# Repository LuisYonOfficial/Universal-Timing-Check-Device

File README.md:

# Universal Timing Check Board (UTCB)
###### This repo acts as the digital storage of all associated developments (e.g. firmware, pcb development, CAD) and related documentation (e.g. schematic captures, pictures, testing data) to the "Universal Timing Check Board". This device acts as a sister companion to circuit testing for analog voltage checks and timing. Inspiration for board function and design is from previous revisions of an analog based brake system plausiblity device, however, this device is more general purpose and for my personal use. 

Current Layout: 

## Board Functionality
- Check if an upper threshold is met. (0v to 12v)
    - Multichannel Comparator check
- Check if a lower threshold is met.
    - Multichannel Comparator check (0v to 12v)
- Check if mid threshold comparison between 6 signals is met. 
    - Mid-threshold voltage set via 6 potentiometers (0v to 12v)
- Drive a failure mode signal out from either signals (Within the range of 3.3-12v)
- Give Flashing Red Light when output failure is detected. Otherwise Solid Red.
- Optional: Has breakout OLED slot for visualizing data in real time with bluetooth connected transmitter. Most likely will use STM32 for MCU. 
    
## Board Connection Points

Main PWR: 
- 12V Power In Connector (Gets reduced to 3.3v via regulator for central comparator logic)
- Final PWR voltage needs to be regulated (Using off the shelf dc/dc converters with built-in regulation)

Signal Connections (For reading)
- Terminal block connection points (6P header) for direct wire feeds. 
- OptionaL: For signal voltage reading: Has ribbon cable attachment to breadboard for data collection (but no direct programmable element on-board). 
- For board debugging: Set test points to grip onto for PWR points, Comparator Outputs, and final failure outputs. 
- Indivdual signals, logic set positions, threshold voltages are passed through to the data collection slot for telemetry. 

## Purpose

- Allows me to isolate analog logic voltages on an offboard device or PCB. 
- Allows me to clearly indicate where faulty logic is based on physical tuning via potentiometers. 
- Gives me an automated way of doing logic checks over set number of iterations on the device under test. 

## What to do next
- Add visual LED indicator for each comparator logic output
- Add optional telemetric side port
- Need to reposition test points so as to not accidently short to pot pins.

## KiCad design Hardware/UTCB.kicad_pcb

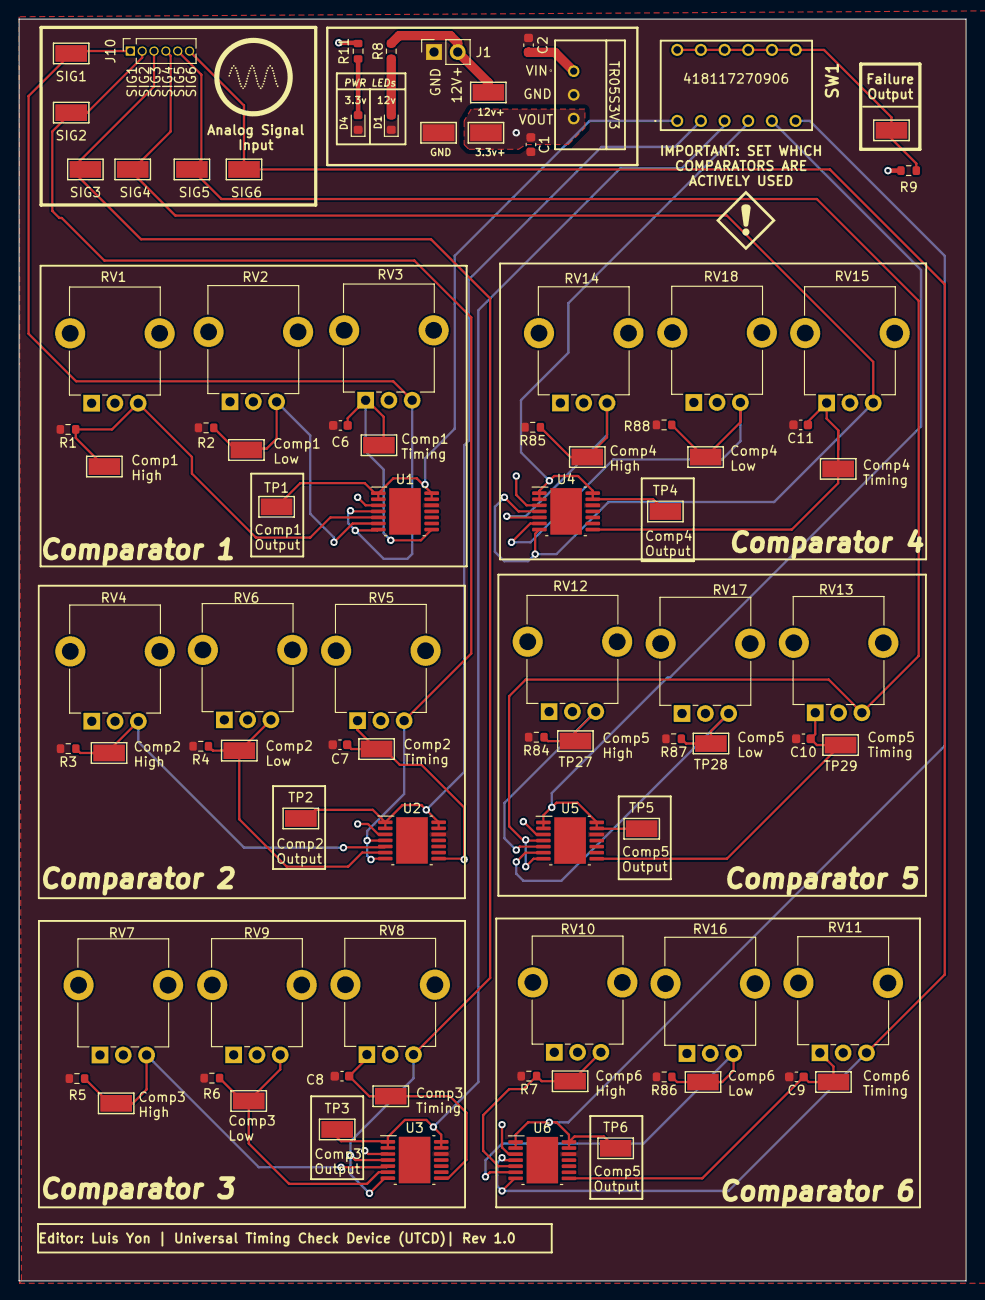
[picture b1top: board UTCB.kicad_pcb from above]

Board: 4 copper layers, 101.6 x 135.4 mm, 87 parts (0 on the bottom side), 36 nets.

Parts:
C1: 47uF; C_0603_1608Metric
C2: 22uF; C_0603_1608Metric
C6, C7, C8, C9, C10, C11: 10uF; C_0603_1608Metric
D1: APT1608SEC/J3-AMT; D_0603_1608Metric
D4: SMLEN3WBC8W1; D_0603_1608Metric
IC1: TR05S3V3
J1: Conn_01x02; PinSocket_1x02_P2.54mm_Vertical
J10: Conn_01x06; PinSocket_1x06_P1.27mm_Vertical
R1, R2, R3, R4, R5, R6, R7, R84, R85, R86, R87, R88: 10kΩ; R_0603_1608Metric
R8, R11: R_Small; R_0603_1608Metric
R9: 1k; R_0603_1608Metric
RV1, RV2, RV4, RV6, RV7, RV9, RV10, RV12, RV14, RV16, RV17, RV18: R_Potentiometer_Trim; Potentiometer_Alpha_RD901F-40-00D_Single_Vertical_CircularH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
RV3, RV5, RV8, RV11, RV13, RV15: 10kΩ; Potentiometer_Alpha_RD901F-40-00D_Single_Vertical_CircularH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
SW1: SW_DIP_x06; 418117270906
TP1: Comp1_Output; TestPoint_Keystone_5015_Micro-Minature
TP2: Comp2_Output; TestPoint_Keystone_5015_Micro-Minature
TP3: Comp3_Output; TestPoint_Keystone_5015_Micro-Minature
TP4: Comp4_Output; TestPoint_Keystone_5015_Micro-Minature
TP5: Comp5_Output; TestPoint_Keystone_5015_Micro-Minature
TP6: Comp6_Output; TestPoint_Keystone_5015_Micro-Minature
TP7: COMP1_HIGH; TestPoint_Keystone_5015_Micro-Minature
TP8: COMP1_LOW; TestPoint_Keystone_5015_Micro-Minature
TP9: COMP1_TIMING; TestPoint_Keystone_5015_Micro-Minature
TP10: COMP2_HIGH; TestPoint_Keystone_5015_Micro-Minature
TP11: COMP2_LOW; TestPoint_Keystone_5015_Micro-Minature
TP12: COMP2_TIMING; TestPoint_Keystone_5015_Micro-Minature
TP13: 12v_Check; TestPoint_Keystone_5015_Micro-Minature
TP14, TP15: COMP3_HIGH; TestPoint_Keystone_5015_Micro-Minature
TP16: 3.3v_Check; TestPoint_Keystone_5015_Micro-Minature
TP17: Signal1_Check; TestPoint_Keystone_5015_Micro-Minature
TP18: Signal2_Check; TestPoint_Keystone_5015_Micro-Minature
TP19: Signal3_Check; TestPoint_Keystone_5015_Micro-Minature
TP20: Signal4_Check; TestPoint_Keystone_5015_Micro-Minature
TP21: Signal5_Check; TestPoint_Keystone_5015_Micro-Minature
TP22: Signal6_Check; TestPoint_Keystone_5015_Micro-Minature
TP23, TP29: COMP3_TIMING; TestPoint_Keystone_5015_Micro-Minature
TP24, TP25: COMP4_HIGH; TestPoint_Keystone_5015_Micro-Minature
TP26: COMP4_TIMING; TestPoint_Keystone_5015_Micro-Minature
TP27, TP28: COMP5_HIGH; TestPoint_Keystone_5015_Micro-Minature
TP30, TP31: COMP6_HIGH; TestPoint_Keystone_5015_Micro-Minature
TP32: COMP6_TIMING; TestPoint_Keystone_5015_Micro-Minature
TP33: Failure_Check; TestPoint_Keystone_5015_Micro-Minature
TP34: GND_Check; TestPoint_Keystone_5015_Micro-Minature
U1, U2, U3, U4, U5, U6: HTSSOP-14-1EP_4.4x5mm_P0.65mm_EP3.4x5mm_Mask3x3.1mm

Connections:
+3.3V: C1.1, IC1.3 (+VOUT), R9.1, R11.1, RV1.1, RV2.1, RV4.1, RV6.1, RV7.1, RV9.1, RV10.1, RV12.1, RV14.1, RV16.1, RV17.1, RV18.1, TP16.1, U1.3 (VCC), U2.3 (VCC), U3.3 (VCC), U4.3 (VCC), U5.3 (VCC), U6.3 (VCC)
+12V: C2.1, IC1.1 (+VIN), J1.2, R8.2, TP13.1
/ComparatorLogic/COMP1_HIGH: R1.1, RV1.3, TP7.1, U1.5 (1IN+)
/ComparatorLogic/COMP1_LOW: R2.1, RV2.3, TP8.1, U1.6 (2IN-)
/ComparatorLogic/COMP2_HIGH: R3.1, RV4.3, TP10.1, U2.5 (1IN+)
/ComparatorLogic/COMP2_LOW: R4.1, RV6.3, TP11.1, U2.6 (2IN-)
/ComparatorLogic/COMP3_HIGH: R5.1, RV7.3, TP14.1, U3.5 (1IN+)
/ComparatorLogic/COMP3_LOW: R6.1, RV9.3, TP15.1, U3.6 (2IN-)
/ComparatorLogic/COMP4_HIGH: R85.1, RV14.3, TP24.1, U4.5 (1IN+)
/ComparatorLogic/COMP4_LOW: R88.1, RV18.3, TP25.1, U4.6 (2IN-)
/ComparatorLogic/COMP5_HIGH: R84.1, RV12.3, TP27.1, U5.5 (1IN+)
/ComparatorLogic/COMP5_LOW: R87.1, RV17.3, TP28.1, U5.6 (2IN-)
/ComparatorLogic/COMP6_HIGH: R7.1, RV10.3, TP30.1, U6.5 (1IN+)
/ComparatorLogic/COMP6_LOW: R86.1, RV16.3, TP31.1, U6.6 (2IN-)
/ComparatorLogic/Failure_Output: R9.2, SW1.7, SW1.8, SW1.9, SW1.10, SW1.11, SW1.12, TP33.1
/ComparatorLogic/Timing1Check: C6.1, RV3.1, TP9.1, U1.8 (3IN-)
/ComparatorLogic/Timing2Check: C7.1, RV5.1, TP12.1, U2.8 (3IN-)
/ComparatorLogic/Timing3Check: C8.1, RV8.1, TP23.1, U3.8 (3IN-)
/ComparatorLogic/Timing4Check: C11.1, RV15.1, TP26.1, U4.8 (3IN-)
/ComparatorLogic/Timing5Check: C10.1, RV13.1, TP29.1, U5.8 (3IN-)
/ComparatorLogic/Timing6Check: C9.1, RV11.1, TP32.1, U6.8 (3IN-)
COMP1A: SW1.1, TP1.1, U1.1 (2OUT), U1.2 (1OUT), U1.13 (4OUT), U1.14 (3OUT)
COMP2A: SW1.2, TP2.1, U2.1 (2OUT), U2.2 (1OUT), U2.13 (4OUT), U2.14 (3OUT)
COMP3A: SW1.3, TP3.1, U3.1 (2OUT), U3.2 (1OUT), U3.13 (4OUT), U3.14 (3OUT)
COMP4A: SW1.4, TP4.1, U4.1 (2OUT), U4.2 (1OUT), U4.13 (4OUT), U4.14 (3OUT)
COMP5A: SW1.5, TP5.1, U5.1 (2OUT), U5.2 (1OUT), U5.13 (4OUT), U5.14 (3OUT)
COMP6A: SW1.6, TP6.1, U6.1 (2OUT), U6.2 (1OUT), U6.13 (4OUT), U6.14 (3OUT)
GND: C1.2, C2.2, C6.2, C7.2, C8.2, C9.2, C10.2, C11.2, D1.1 (K), D4.1 (K), IC1.2 (GND), J1.1, R1.2, R2.2, R3.2, R4.2, R5.2, R6.2, R7.2, R84.2, R85.2, R86.2, R87.2, R88.2, TP34.1, U1.12 (VIN-), U2.12 (VIN-), U3.12 (VIN-), U4.12 (VIN-), U5.12 (VIN-), U6.12 (VIN-)
unnamed: D1.2 (A), R8.1
unnamed: D4.2 (A), R11.2
Signal1: J10.1, RV3.3, TP17.1, U1.4 (1IN-), U1.7 (2IN+)
Signal2: J10.2, RV5.3, TP18.1, U2.4 (1IN-), U2.7 (2IN+)
Signal3: J10.3, RV8.3, TP19.1, U3.4 (1IN-), U3.7 (2IN+)
Signal4: J10.4, RV15.3, TP20.1, U4.4 (1IN-), U4.7 (2IN+)
Signal5: J10.5, RV13.3, TP21.1, U5.4 (1IN-), U5.7 (2IN+)
Signal6: J10.6, RV11.3, TP22.1, U6.4 (1IN-), U6.7 (2IN+)

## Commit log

2023-02-27 README.md
    Basic description + general thoughts
2023-02-27 Update README.md
    added image for pseudo estimate of potentiometer and board layout
2023-02-27 Update README.md
    Added note for multichannel comparators
2023-02-27 Update README.md
    added programmable slot
2023-02-28 Added changes for initial logic comparisons
2023-02-28 Reorganized folders
2023-03-01 Added changes to pseudocode
2023-03-02 Added some changes for the logic switching circuitry. Will be adding thyristor or cascaded bjt configuration for various lighting types for each logic level
2023-03-03 Completed Logic Selector page with respec to rotary switches and LED tied to selected voltage levels
2023-03-03 Added 3D models
2023-03-03 Update README.md
    Updated todo list
2023-03-07 Added updates to pcb file and timing logic
2023-03-07 Added updates to logic switches for timing based logic. Updated attached 3D models.
2023-03-07 Added changes to logic timing
2023-03-22 Added changes to logic side for comparator inputs
2023-03-22 Removed a lot of unnecessary BJT logic, removed rotary switches for logic setting (set all to universal final 3.3v based logic)
2023-03-22 Update README.md
    Added images to readme
2023-03-22 Update README.md
    removed unnecessary bulletpoints in readme
2023-03-22 Update README.md
    Added mention of removing timing checks for certain logic stages
2023-03-23 Update README.md
    moved images in readme
2023-03-23 Added dip switch for comparator active selection
2023-03-23 Update README.md
    Added new updated 3d model
2023-03-23 Continued traces for layout
2023-03-26 Added additional trace routing
2023-03-26 Organized main sheet
2023-03-27 Organized schematic outline
    Misc. changes to schematic.
2023-04-03 Completed rev1.0 traces
    Finished traces
2023-04-03 Minor modifications
    Added 3D model for the regulator, updated to socket for signal inputs, and updated to power pours for certain PWR pins.
2023-04-03 Updated README
    Added images.
2023-04-03 Updated readme
    added note to change test point positions
2023-04-08 Misc Update
    Minor update (just updating previous revision path)
